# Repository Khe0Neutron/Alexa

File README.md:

# Proyecto de Control de Luces con Alexa

Este proyecto permite controlar hasta ocho luces en una casa utilizando comandos de voz a través de Amazon Alexa. Está basado en un ESP32, que se conecta a la red WiFi para recibir las órdenes desde Alexa. También se pueden controlar las luces manualmente utilizando botones físicos conectados al ESP32.

## Características

- **Control de luces con Alexa**: Puedes encender y apagar las luces utilizando comandos de voz.
- **Control manual**: Cada luz puede ser controlada manualmente mediante botones físicos conectados al ESP32.
- **Retroalimentación de estado**: El ESP32 proporciona retroalimentación del estado de cada luz tanto a través de la consola serial como del estado del relé.
- **Configuración flexible**: Los nombres de los dispositivos (luces) se pueden personalizar en el código.

## Requisitos

- **Hardware:**
  - ESP32
  - 8 relés para controlar las luces
  - 8 botones físicos para control manual
  - LED para indicar estado de conexión WiFi
  - Conexión WiFi

- **Librerías Arduino:**
  - [`WiFi.h`](https://github.com/espressif/arduino-esp32/tree/master/libraries/WiFi)
  - [`Espalexa.h`](https://github.com/Aircoookie/Espalexa)
  - [`AceButton.h`](https://github.com/bxparks/AceButton)

## Configuración del Hardware

- Los pines del ESP32 están conectados a los relés y a los botones físicos. Aquí están las asignaciones de pines utilizadas en el proyecto:
  - **Relés:**
    - Relé 1: GPIO 23
    - Relé 2: GPIO 22
    - Relé 3: GPIO 21
    - Relé 4: GPIO 19
    - Relé 5: GPIO 18
    - Relé 6: GPIO 5
    - Relé 7: GPIO 25
    - Relé 8: GPIO 26
  - **Botones:**
    - Botón 1: GPIO 13
    - Botón 2: GPIO 12
    - Botón 3: GPIO 14
    - Botón 4: GPIO 27
    - Botón 5: GPIO 33
    - Botón 6: GPIO 32
    - Botón 7: GPIO 15
    - Botón 8: GPIO 4
  - **LED de estado WiFi:** GPIO 2

## Instalación y Configuración

1. **Instalación de librerías:**
   - Asegúrate de tener instaladas las librerías mencionadas en la sección de requisitos.

2. **Configuración de WiFi:**
   - Modifica las siguientes líneas en el código para configurar tu red WiFi:
     ```cpp
     const char* ssid = "Red"; // Cambiar nombre de red
     const char* password = "Contraseña"; // Cambiar contraseña de red
     ```

3. **Compilación y carga:**
   - Compila y sube el código al ESP32 utilizando el IDE de Arduino.

4. **Integración con Alexa:**
   - Una vez que el ESP32 esté conectado a la red WiFi, Alexa detectará los dispositivos automáticamente. Puedes controlar las luces diciendo comandos como "Alexa, enciende la luz de la sala".

## Uso

- **Control con Alexa:** Di "Alexa, enciende/apaga [nombre de la luz]" para controlar las luces.
- **Control manual:** Pulsa el botón físico correspondiente para encender o apagar una luz.

## Contribución

Si encuentras algún error o tienes sugerencias para mejorar el proyecto, siéntete libre de abrir un issue o hacer un pull request.

## Funcionamiento

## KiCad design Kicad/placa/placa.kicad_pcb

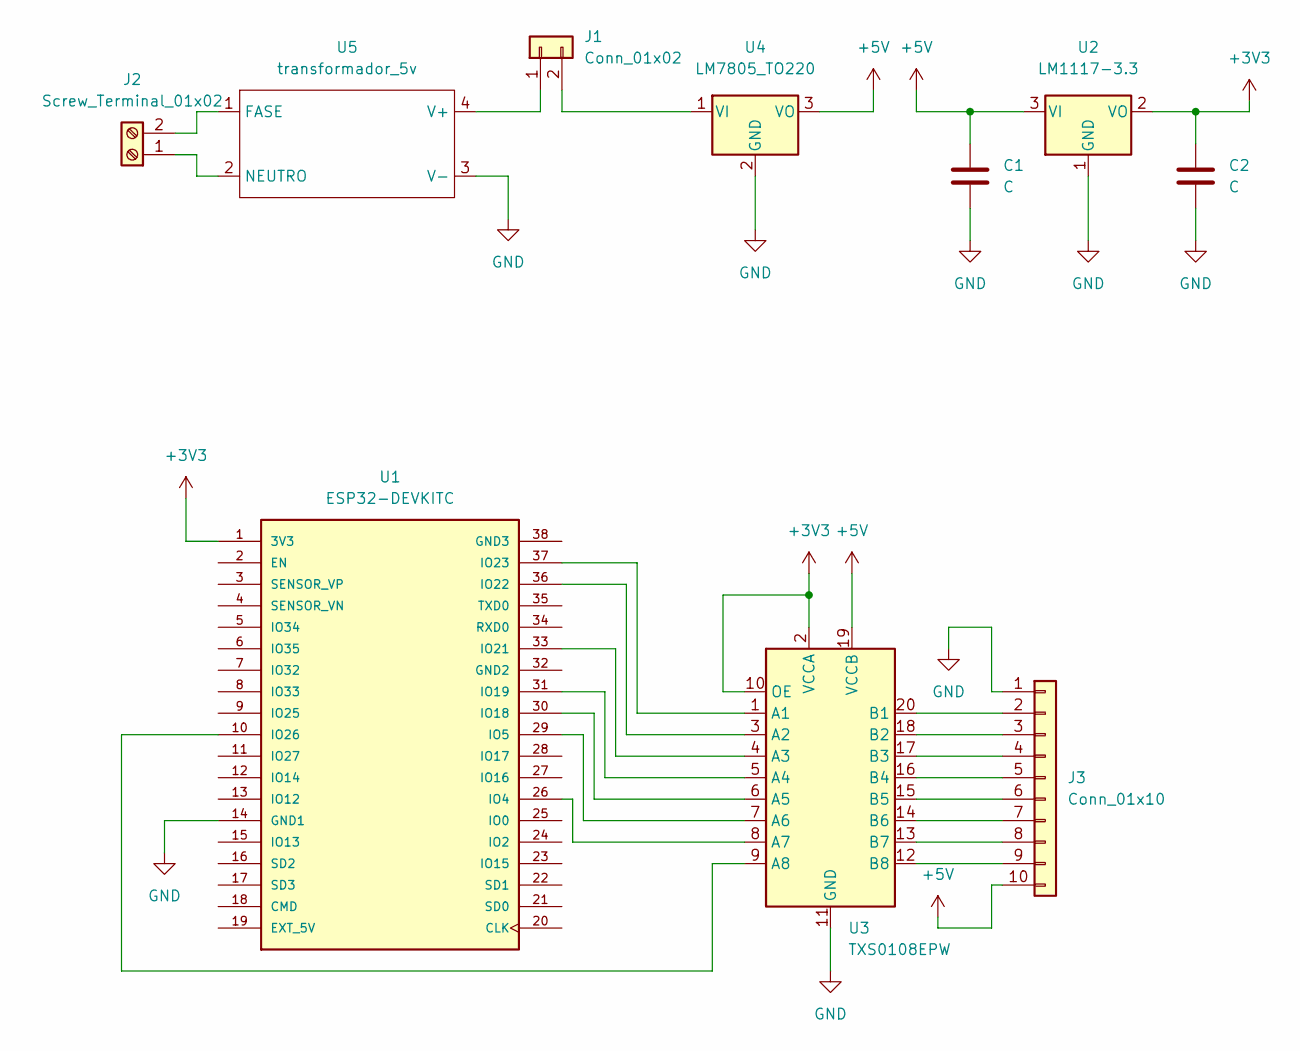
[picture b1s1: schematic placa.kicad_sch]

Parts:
C1, C2: C; CP_Radial_D4.0mm_P2.00mm
J1: Conn_01x02; PinHeader_1x02_P2.54mm_Vertical
J2: Screw_Terminal_01x02; TerminalBlock_bornier-2_P5.08mm
J3: Conn_01x10; PinHeader_1x10_P2.54mm_Vertical
U1: ESP32-DEVKITC; MODULE_ESP32-DEVKITC; PARTREV N/A
U2: LM1117-3.3; TO254P1054X470X1955-3
U3: TXS0108EPW; txs0108
U4: LM7805_TO220; TO-220-3_Vertical
U5: transformador_5v; TRANSFORMADOR 5V

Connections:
+3V3: C2.1, U1.1 (3V3), U2.2 (VO), U3.2 (VCCA), U3.10 (OE)
+5V: C1.1, J3.10, U2.3 (VI), U3.19 (VCCB), U4.3 (VO)
GND: C1.2, C2.2, J3.1, U1.14 (GND1), U2.1 (GND), U3.11 (GND), U4.2 (GND), U5.3 (V-)
unnamed: J1.1, U5.4 (V+)
unnamed: J1.2, U4.1 (VI)
unnamed: J2.1, U5.2 (NEUTRO)
unnamed: J2.2, U5.1 (FASE)
unnamed: J3.2, U3.20 (B1)
unnamed: J3.3, U3.18 (B2)
unnamed: J3.4, U3.17 (B3)
unnamed: J3.5, U3.16 (B4)
unnamed: J3.6, U3.15 (B5)
unnamed: J3.7, U3.14 (B6)
unnamed: J3.8, U3.13 (B7)
unnamed: J3.9, U3.12 (B8)
unnamed: U1.10 (IO26), U3.9 (A8)
unnamed: U1.26 (IO4), U3.8 (A7)
unnamed: U1.29 (IO5), U3.7 (A6)
unnamed: U1.30 (IO18), U3.6 (A5)
unnamed: U1.31 (IO19), U3.5 (A4)
unnamed: U1.33 (IO21), U3.4 (A3)
unnamed: U1.36 (IO22), U3.3 (A2)
unnamed: U1.37 (IO23), U3.1 (A1)

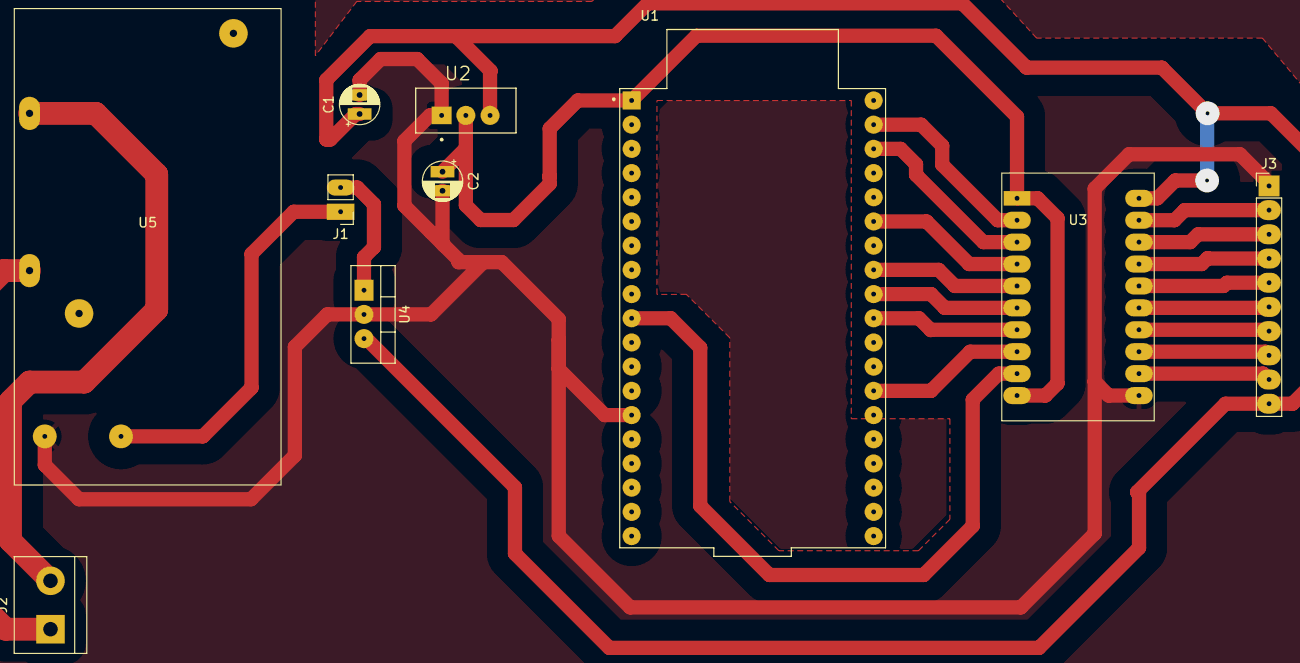
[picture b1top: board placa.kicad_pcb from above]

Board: 2 copper layers, 10 parts (0 on the bottom side), 23 nets.

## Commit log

2024-09-02 Primer COmmit
